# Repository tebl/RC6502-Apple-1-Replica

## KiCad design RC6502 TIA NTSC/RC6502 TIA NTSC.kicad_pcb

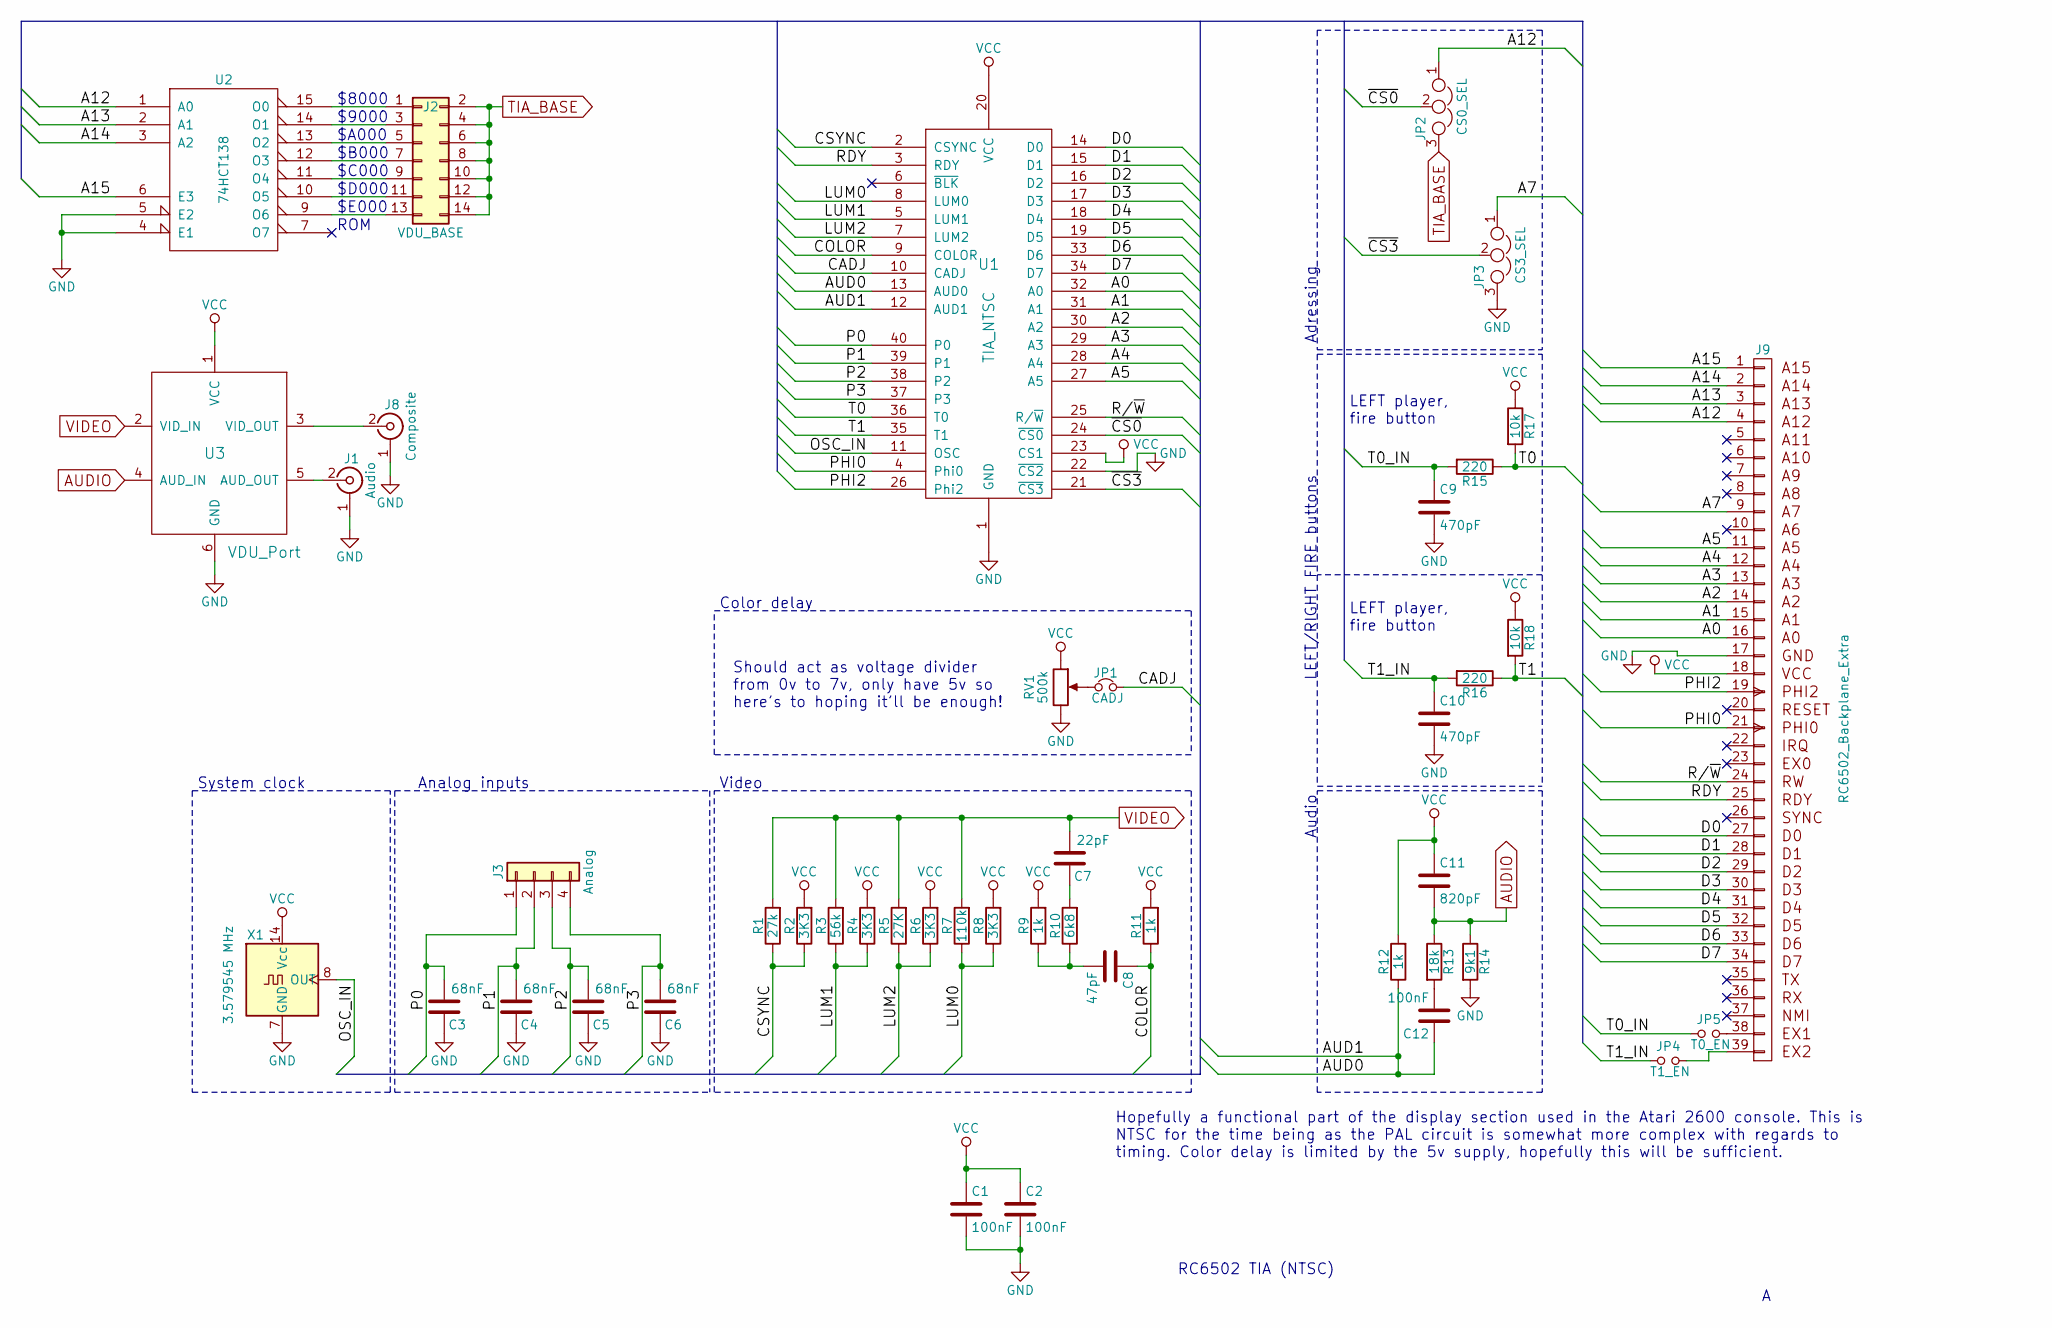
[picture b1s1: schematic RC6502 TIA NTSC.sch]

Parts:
C1, C2, C12: 100nF; C_Disc_D4.7mm_W2.5mm_P5.00mm
C3, C4, C5, C6: 68nF; C_Disc_D4.7mm_W2.5mm_P5.00mm
C7: 22pF; C_Disc_D4.7mm_W2.5mm_P5.00mm
C8: 47pF; C_Disc_D4.7mm_W2.5mm_P5.00mm
C9, C10: 470pF; C_Disc_D4.7mm_W2.5mm_P5.00mm
C11: 820pF; C_Disc_D4.7mm_W2.5mm_P5.00mm
J1: Audio; rca_yellow
J2: VDU_BASE; Pin_Header_Straight_2x07_Pitch2.54mm
J3: Analog; Pin_Header_Straight_1x04_Pitch2.54mm
J8: Composite; rca_yellow
J9: RC6502_Backplane_Extra; Pin_Header_Angled_1x39_Pitch2.54mm
JP1: CADJ; Pin_Header_Straight_1x02_Pitch2.54mm
JP2: CS0_SEL; Pin_Header_Straight_1x03_Pitch2.54mm
JP3: CS3_SEL; Pin_Header_Straight_1x03_Pitch2.54mm
JP4: T1_EN; Pin_Header_Straight_1x02_Pitch2.54mm
JP5: T0_EN; Pin_Header_Straight_1x02_Pitch2.54mm
R1: 27k; R_Axial_DIN0207_L6.3mm_D2.5mm_P10.16mm_Horizontal
R2, R4, R6, R8: 3K3; R_Axial_DIN0207_L6.3mm_D2.5mm_P10.16mm_Horizontal
R3: 56k; R_Axial_DIN0207_L6.3mm_D2.5mm_P10.16mm_Horizontal
R5: 27K; R_Axial_DIN0207_L6.3mm_D2.5mm_P10.16mm_Horizontal
R7: 110k; R_Axial_DIN0207_L6.3mm_D2.5mm_P10.16mm_Horizontal
R9, R11, R12: 1k; R_Axial_DIN0207_L6.3mm_D2.5mm_P10.16mm_Horizontal
R10: 6k8; R_Axial_DIN0207_L6.3mm_D2.5mm_P10.16mm_Horizontal
R13: 18k; R_Axial_DIN0207_L6.3mm_D2.5mm_P10.16mm_Horizontal
R14: 9k1; R_Axial_DIN0207_L6.3mm_D2.5mm_P10.16mm_Horizontal
R15, R16: 220; R_Axial_DIN0207_L6.3mm_D2.5mm_P10.16mm_Horizontal
R17, R18: 10k; R_Axial_DIN0207_L6.3mm_D2.5mm_P10.16mm_Horizontal
RV1: 500k; Potentiometer_Trimmer_Bourns_3296W
U1: TIA_NTSC; DIP-40_W15.24mm_Socket
U2: 74HCT138; DIP-16_W7.62mm_Socket
U3: VDU_Port; Amplifier
X1: 3.579545 MHz; Oscillator_DIP-14

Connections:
/A0: J9.16 (A0), U1.32 (A0)
/A1: J9.15 (A1), U1.31 (A1)
/A2: J9.14 (A2), U1.30 (A2)
/A3: J9.13 (A3), U1.29 (A3)
/A4: J9.12 (A4), U1.28 (A4)
/A5: J9.11 (A5), U1.27 (A5)
/A7: J9.9 (A7), JP3.1
/A12: J9.4 (A12), JP2.1, U2.1 (A0)
/A13: J9.3 (A13), U2.2 (A1)
/A14: J9.2 (A14), U2.3 (A2)
/A15: J9.1 (A15), U2.6 (E3)
/AUD0: C12.1, R12.1, U1.12 (AUD1), U1.13 (AUD0)
/CADJ: JP1.2, U1.10 (CADJ)
/COLOR: C8.1, R11.1, U1.9 (COLOR)
/CSYNC: R1.1, R2.1, U1.2 (CSYNC)
/D0: J9.27 (D0), U1.14 (D0)
/D1: J9.28 (D1), U1.15 (D1)
/D2: J9.29 (D2), U1.16 (D2)
/D3: J9.30 (D3), U1.17 (D3)
/D4: J9.31 (D4), U1.18 (D4)
/D5: J9.32 (D5), U1.19 (D5)
/D6: J9.33 (D6), U1.33 (D6)
/D7: J9.34 (D7), U1.34 (D7)
/LUM0: R7.1, R8.1, U1.8 (LUM0)
/LUM1: R3.1, R4.1, U1.5 (LUM1)
/LUM2: R5.1, R6.1, U1.7 (LUM2)
/OSC_IN: U1.11 (OSC), X1.8 (OUT)
/P0: C3.2, J3.1, U1.40 (P0)
/P1: C4.2, J3.2, U1.39 (P1)
/P2: C5.2, J3.3, U1.38 (P2)
/P3: C6.2, J3.4, U1.37 (P3)
/PHI0: J9.21 (PHI0), U1.4 (Phi0)
/PHI2: J9.19 (PHI2), U1.26 (Phi2)
/R/~W: J9.24 (RW), U1.25 (R/~W)
/RDY: J9.25 (READY), U1.3 (RDY)
/T0: R15.1, R17.2, U1.36 (T0)
/T0_IN: C9.1, JP5.1, R15.2
/T1: R16.1, R18.2, U1.35 (T1)
/T1_IN: C10.1, JP4.1, R16.2
/~CS0: JP2.2, U1.24 (~CS0)
/~CS3: JP3.2, U1.21 (~CS3)
AUDIO: C11.2, R13.1, R14.1, U3.4 (AUD_IN)
GND: C1.2, C2.2, C3.1, C4.1, C5.1, C6.1, C9.2, C10.2, J1.1 (Ext), J8.1 (Ext), J9.17, JP3.3, R14.2, RV1.3, U1.1 (GND), U1.22 (~CS2), U2.4 (E1), U2.5 (E2), U2.8 (GND), U3.6 (GND), X1.7 (GND)
unnamed: C7.1, R10.2
unnamed: C8.2, R9.1, R10.1
unnamed: C12.2, R13.2
unnamed: J1.2 (In), U3.5 (AUD_OUT)
unnamed: J2.1, U2.15 (O0)
unnamed: J2.3, U2.14 (O1)
unnamed: J2.5, U2.13 (O2)
unnamed: J2.7, U2.12 (O3)
unnamed: J2.9, U2.11 (O4)
unnamed: J2.11, U2.10 (O5)
unnamed: J2.13, U2.9 (O6)
unnamed: J8.2 (In), U3.3 (VID_OUT)
unnamed: J9.38 (EX1), JP5.2
unnamed: J9.39 (EX2), JP4.2
unnamed: JP1.1, RV1.2
TIA_BASE: J2.2, J2.4, J2.6, J2.8, J2.10, J2.12, J2.14, JP2.3
VCC: C1.1, C2.1, C11.1, J9.18, R2.2, R4.2, R6.2, R8.2, R9.2, R11.2, R12.2, R17.1, R18.1, RV1.1, U1.20 (VCC), U1.23 (CS1), U2.16 (VCC), U3.1 (VCC), X1.14 (Vcc)
VIDEO: C7.2, R1.2, R3.2, R5.2, R7.2, U3.2 (VID_IN)

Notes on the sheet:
RC6502 TIA (NTSC)
ROM
$C000
$B000
$A000
$9000
$8000
$D000
$E000
LEFT player, fire button
Video
Analog inputs
System clock
Audio
LEFT/RIGHT FIRE buttons
Adressing
Color delay
Should act as voltage divider from 0v to 7v, only have 5v so here's to hoping it'll be enough!
Hopefully a functional part of the display section used in the Atari 2600 console. This is NTSC for the time being as the PAL circuit is somewhat more complex with regards to timing. Color delay is limited by the 5v supply, hopefully this will be sufficient.

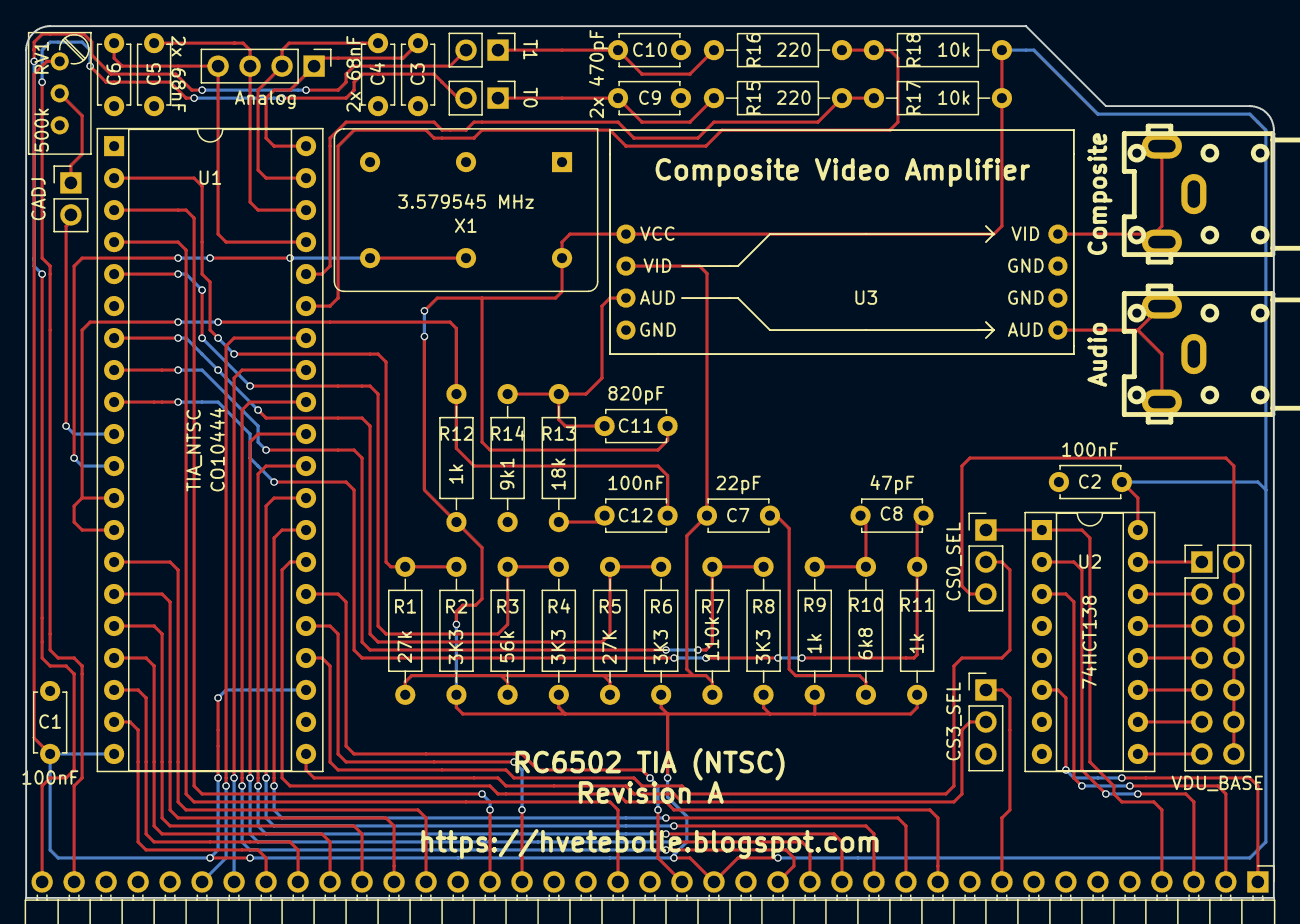
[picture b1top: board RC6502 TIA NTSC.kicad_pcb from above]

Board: 2 copper layers, 99.1 x 69.2 mm, 45 parts (0 on the bottom side), 61 nets.

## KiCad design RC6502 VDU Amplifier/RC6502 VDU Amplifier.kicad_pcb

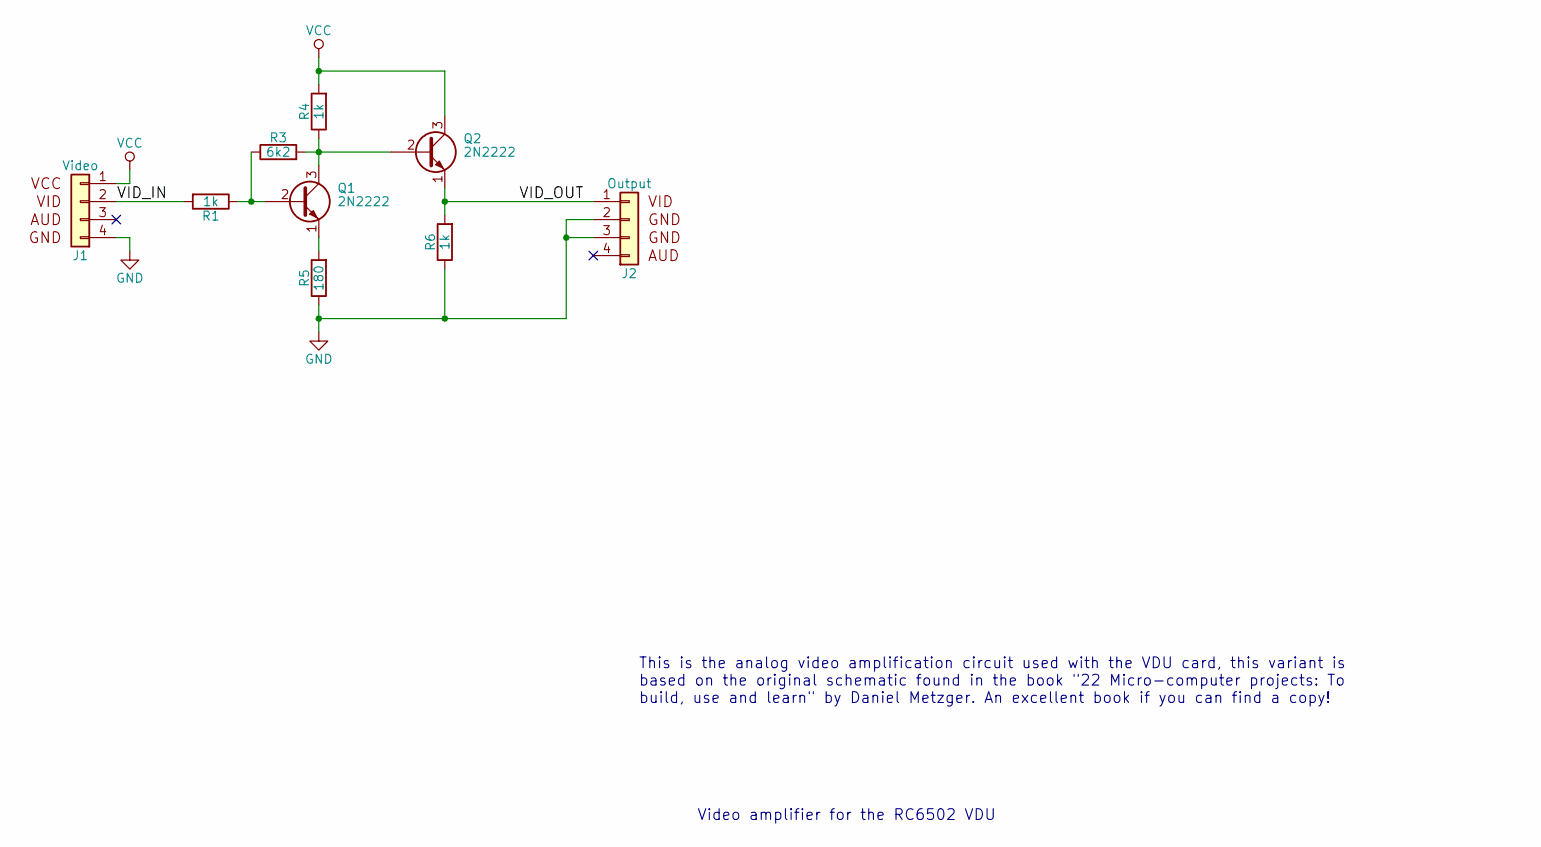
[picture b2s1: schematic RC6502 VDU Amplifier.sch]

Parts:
J1: Video; Pin_Header_Straight_1x04_Pitch2.54mm
J2: Output; Pin_Header_Straight_1x04_Pitch2.54mm
Q1, Q2: 2N2222; TO-92_Inline_Wide
R1, R4, R6: 1k; R_Axial_DIN0207_L6.3mm_D2.5mm_P10.16mm_Horizontal
R3: 6k2; R_Axial_DIN0207_L6.3mm_D2.5mm_P10.16mm_Horizontal
R5: 180; R_Axial_DIN0207_L6.3mm_D2.5mm_P10.16mm_Horizontal

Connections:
/VID_IN: J1.2 (Pin_3), R1.2
/VID_OUT: J2.1 (Pin_4), Q2.1 (E), R6.2
GND: J1.4 (Pin_1), J2.2 (Pin_3), J2.3 (Pin_2), R5.1, R6.1
unnamed: Q1.1 (E), R5.2
unnamed: Q1.2 (B), R1.1, R3.1
unnamed: Q1.3 (C), Q2.2 (B), R3.2, R4.1
VCC: J1.1 (Pin_4), Q2.3 (C), R4.2

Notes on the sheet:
This is the analog video amplification circuit used with the VDU card, this variant is based on the original schematic found in the book "22 Micro-computer projects: To build, use and learn" by Daniel Metzger. An excellent book if you can find a copy!
Video amplifier for the RC6502 VDU

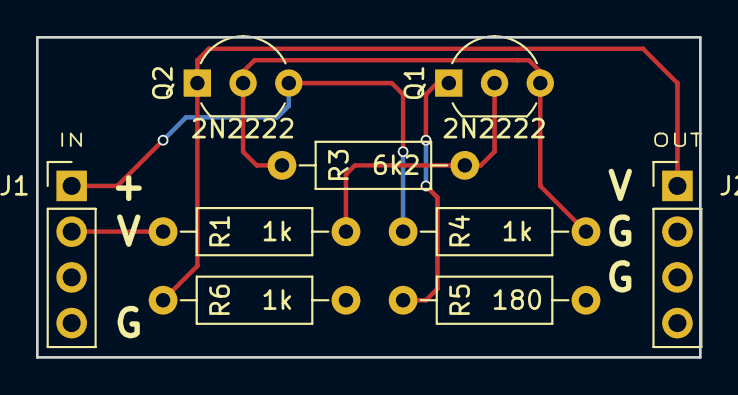
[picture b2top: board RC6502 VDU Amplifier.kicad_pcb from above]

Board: 2 copper layers, 36.8 x 17.8 mm, 9 parts (0 on the bottom side), 7 nets.

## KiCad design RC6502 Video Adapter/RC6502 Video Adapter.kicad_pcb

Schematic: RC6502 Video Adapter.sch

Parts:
C1, C2, C5, C6: 100nF; C_Disc_D4.7mm_W2.5mm_P5.00mm
C3, C4: 22pF; C_Disc_D4.7mm_W2.5mm_P5.00mm
D1, D2: 1N4848; D_DO-35_SOD27_P7.62mm_Horizontal
J1: CONN_01X39; Pin_Header_Angled_1x39_Pitch2.54mm
J2: Peripheral Bus; IDC_Header_Straight_40pins
J3: Video; rca_yellow
J4: FTDI; Pin_Header_Angled_1x06_Pitch2.54mm
J5: ICSP; Pin_Header_Straight_2x03_Pitch2.54mm
J6: General Video Connector; IDC_Header_Straight_40pins
JP1: PullDown; Pin_Header_Straight_1x02_Pitch2.54mm
JP2: Power; Pin_Header_Angled_1x02_Pitch2.54mm
R1: 1k; R_Axial_DIN0207_L6.3mm_D2.5mm_P10.16mm_Horizontal
R2: 330; R_Axial_DIN0207_L6.3mm_D2.5mm_P10.16mm_Horizontal
R3: 75; R_Axial_DIN0207_L6.3mm_D2.5mm_P10.16mm_Horizontal
R4, R5: 10k; R_Axial_DIN0207_L6.3mm_D2.5mm_P10.16mm_Horizontal
U1: ATMEGA328P-PU; DIP-28_W7.62mm_Socket
U2, U3: MCP23S17; DIP-28_W7.62mm_Socket
Y1: 16 Mhz; Crystal_HC49-4H_Vertical

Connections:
GND: C1.1, C3.1, C4.1, C5.1, C6.1, J1.17, J2.2, J2.19, J2.22, J2.26, J2.30, J2.32, J2.40, J3.1 (Ext), J4.1, J4.2, J5.6, J6.1, J6.2, J6.39, J6.40, R3.1, U1.8 (GND), U1.22 (GND), U2.10, U2.15, U2.16, U2.17, U3.8, U3.10, U3.16, U3.17
GV_A0: J6.20, U2.28
GV_A1: J6.22, U2.27
GV_A2: J6.24, U2.26
GV_A3: J6.26, U2.25
GV_A4: J6.28, U2.24
GV_A5: J6.30, U2.23
GV_A6: J6.32, U2.22
GV_A7: J6.34, U2.21
GV_A8: J6.19, U2.8
GV_A9: J6.21, U2.7
GV_A10: J6.23, U2.6
GV_A11: J6.25, U2.5
GV_A12: J6.27, U2.4
GV_A13: J6.29, U2.3
GV_CS: J6.11, U1.23 ((PCINT8/ADC0)PC0)
GV_D0: J6.4, U3.21
GV_D1: J6.6, U3.22
GV_D2: J6.8, U3.23
GV_D3: J6.10, U3.24
GV_D4: J6.12, U3.25
GV_D5: J6.14, U3.26
GV_D6: J6.16, U3.27
GV_D7: J6.18, U3.28
GV_DETECT: J6.37, R5.1, U1.26 ((PCINT11/ADC3)PC3)
GV_E: J6.38, U1.25 ((PCINT10/ADC2)PC2)
GV_RW: J6.36, U1.24 ((PCINT9/ADC1)PC1)
MISO: J5.1, U1.18 ((PCINT4/MISO)PB4), U2.14, U3.14
MOSI: J5.4, U1.17 ((PCINT3/OC2A/MOSI)PB3), U2.13, U3.13
unnamed: C2.1, J4.6
unnamed: D1.1 (K), R1.2
unnamed: D2.1 (K), R2.2
unnamed: J3.2 (In), JP1.2, R1.1, R2.1
unnamed: J4.3, JP2.2
unnamed: J4.4, R4.1
unnamed: JP1.1, R3.2
OUT_D0: J2.17, U3.1
OUT_D1: J2.15, U3.2
OUT_D2: J2.13, U3.3
OUT_D3: J2.11, U3.4
OUT_D4: J2.9, U3.5
OUT_D5: J2.7, U3.6
OUT_D6: J2.5, U3.7
OUT_DA: J2.3, U1.5 ((PCINT19/OC2B/INT1)PD3)
OUT_RDA: J2.34, U1.4 ((PCINT18/INT0)PD2)
P_RESET: C2.2, J2.36, J5.5, U1.1 ((PCINT14/~RESET~)PC6), U2.18, U3.18
RCA_SYNC: D1.2 (A), U1.15 ((PCINT1/OC1A)PB1)
RCA_VIDEO: D2.2 (A), U1.13 ((PCINT23/AIN1)PD7)
RX: J1.36, J4.5, U1.3 ((PCINT17/TXD)PD1)
SCK: J5.3, U1.19 ((PCINT5/SCK)PB5), U2.12, U3.12
SS: U1.16 ((PCINT2/OC1B/~SS~)PB2), U2.11, U3.11
TX: J1.35, R4.2, U1.2 ((PCINT16/RXD)PD0)
VCC: C1.2, C5.2, C6.2, J1.18, J5.2, JP2.1, R5.2, U1.7 (VCC), U1.20 (AVCC), U2.9, U3.9, U3.15
XTAL1: C3.2, U1.9 ((PCINT6/XTAL1/TOSC1)PB6), Y1.1
XTAL2: C4.2, U1.10 ((PCINT7/XTAL2/TOSC2)PB7), Y1.2

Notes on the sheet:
RC6502 Video Adapter
Handles interacting with the PIA via the peripheral bus, substituting the original Apple 1 monitor circuitry. Includes General Video Connector as a means of interacting with other custom display modules implemented.

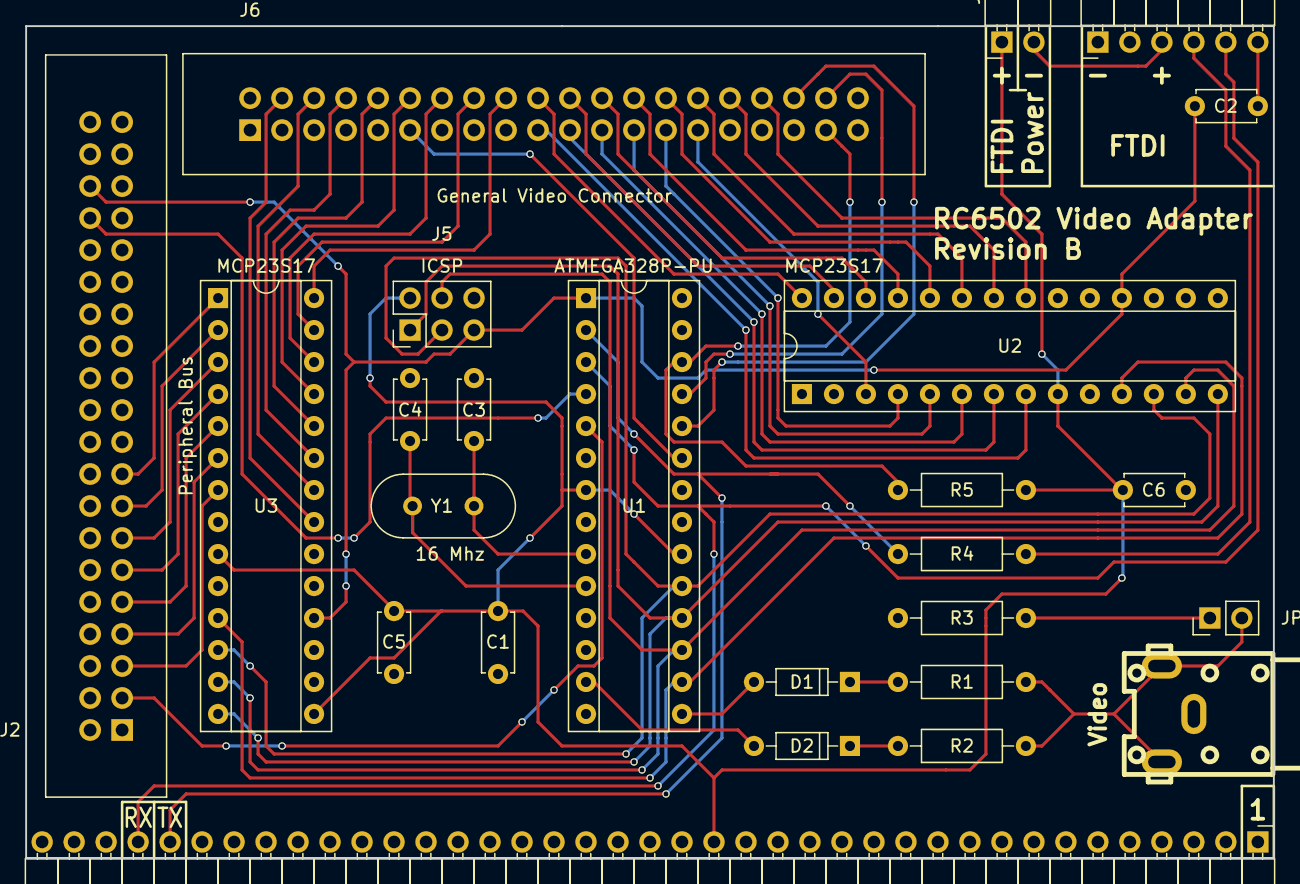
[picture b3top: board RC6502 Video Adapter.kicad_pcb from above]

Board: 2 copper layers, 99.1 x 66.0 mm, 25 parts (0 on the bottom side), 55 nets.
